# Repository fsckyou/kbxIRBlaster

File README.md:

# What the fork?
Yep, this project is a fork of the fantastic open hardware designed by Keith Burzinkski. Check out [the awesome design that this fork is based on](https://github.com/kbx81/kbxIRBlaster)! In many ways, this project is inferior to what he made, but intentionally inferior!

# Why the fork?
I used to buy Tuya IR blasters, pop them open and re-flash the firmware with ESPhome Like many IoT folks used to do. Then they stopped including wifi modules compatible with ESPhome. Well, left with no alternative, I guess I'll have to make them myself! A quick search found Keith's project which met most of my goals, but he designed it for high quality, maximum flexibility, and convenience of the user. My goal is primarily low cost, similarity to the old Tuya products, and bonus points if it can be assembled by JLC PCB.

# kbx and fsckyou IR Blaster

## What?

Just another ESP8266-based IR Blaster. It was designed with
 [ESPHome](https://esphome.io) in mind but should work fine with
 [Tasmota](https://tasmota.github.io/docs/) or any other app, really.

This design is round and should be pretty omnidirectional similar to the Tuya products you can buy on Amazon or Aliexpress.

I'll post images once I have them produced. As of now, this is only a design in progress.

## How?

I'll fill this part in later once the design is more final. ;)

 ## Legal stuff and License

The circuit schematics and PCB found here are licensed under the
 [Creative Commons Attribution-ShareAlike 4.0 International License](http://creativecommons.org/licenses/by-sa/4.0/).

_Happy building!_

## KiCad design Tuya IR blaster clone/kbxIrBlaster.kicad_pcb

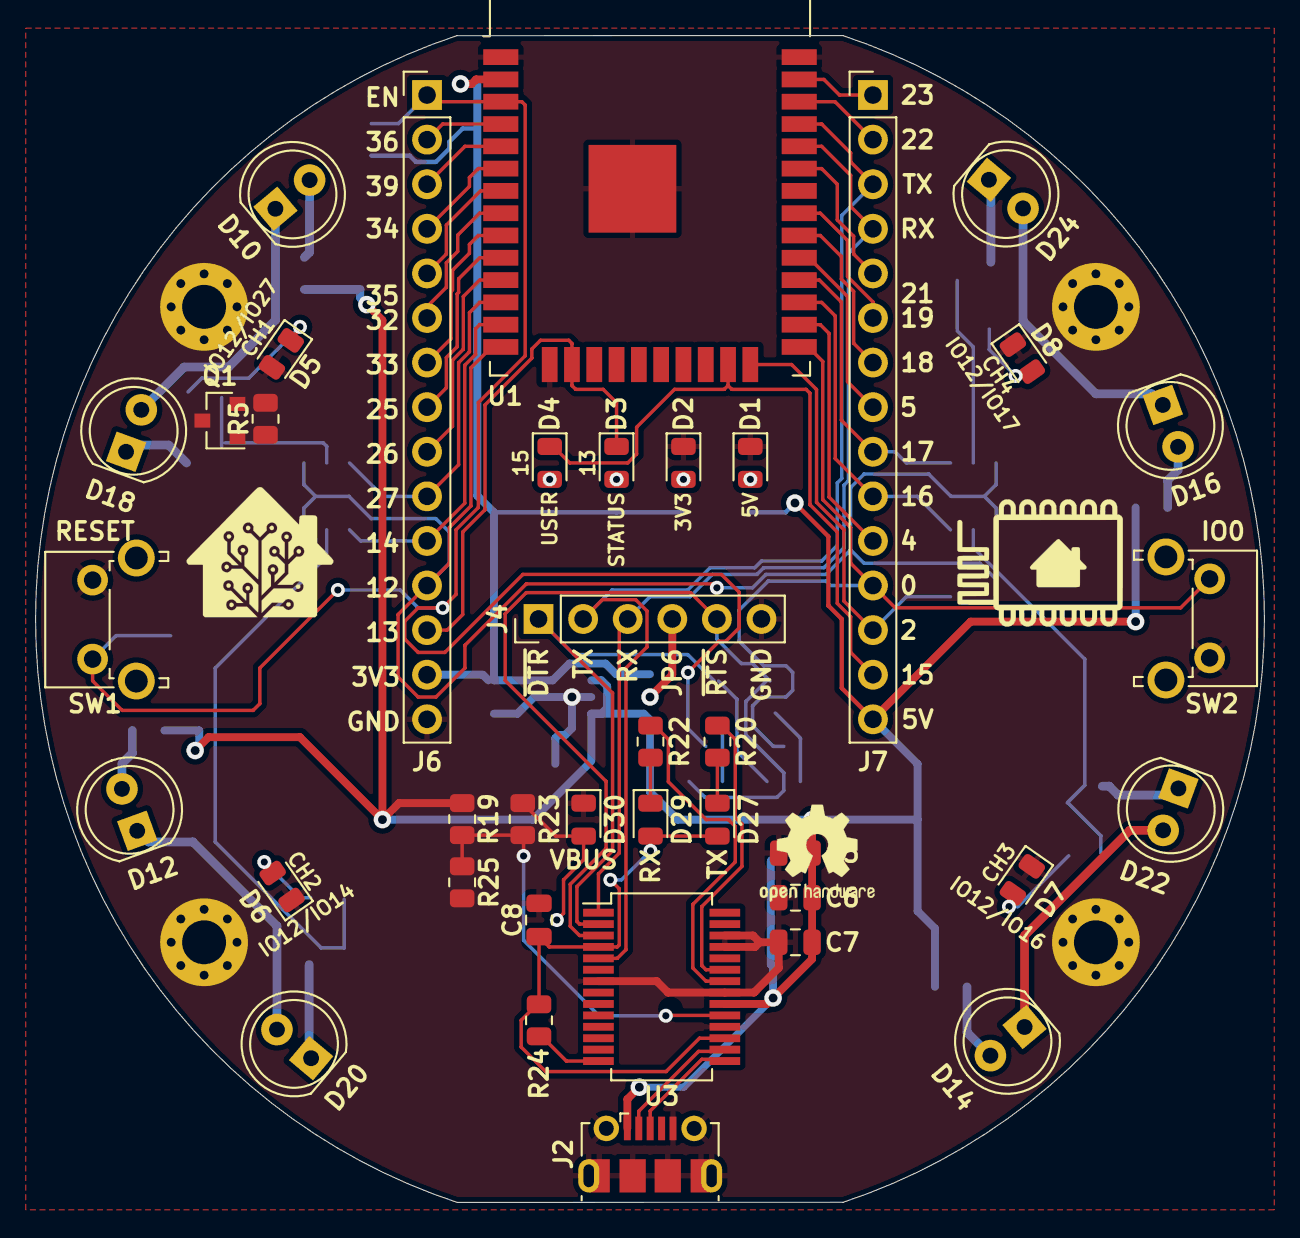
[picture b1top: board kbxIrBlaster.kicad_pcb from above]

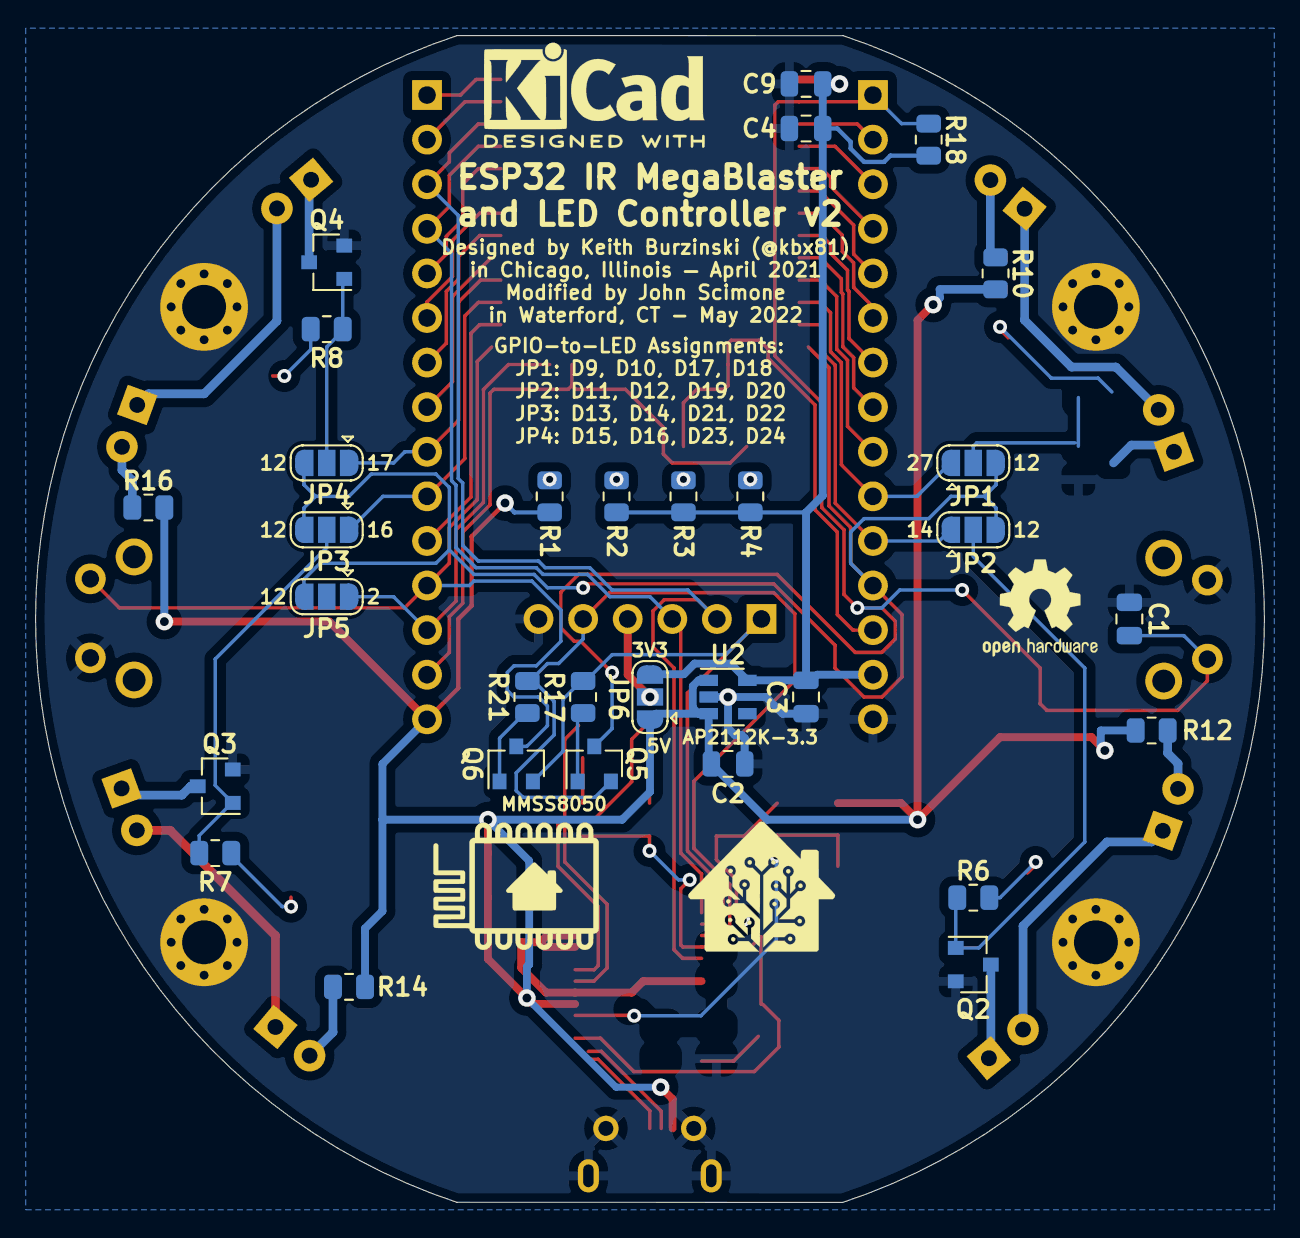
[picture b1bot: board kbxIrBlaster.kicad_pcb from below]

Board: 2 copper layers, 70.0 x 66.5 mm, 74 parts (31 on the bottom side), 69 nets.

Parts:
C1: 1 uF; C_0805_2012Metric
C2, C3, C4, C9: 10 uF; C_0805_2012Metric
C5: 4.7 uF; C_0805_2012Metric
C6, C7, C8: 100 nF; C_0805_2012Metric
D1: 5V; LED_0805_2012Metric
D2: 3V3; LED_0805_2012Metric
D3: STATUS; LED_0805_2012Metric
D4: USER; LED_0805_2012Metric
D5: CH1; LED_0805_2012Metric
D6: CH2; LED_0805_2012Metric
D7: CH3; LED_0805_2012Metric
D8: CH4; LED_0805_2012Metric
D10, D18: CH1; LED_D5.0mm
D12, D20: CH2; LED_D5.0mm
D14, D22: CH3; LED_D5.0mm
D16, D24: CH4; LED_D5.0mm
D27: TX; LED_0805_2012Metric
D29: RX; LED_0805_2012Metric
D30: VBUS; LED_0805_2012Metric
H1, H2, H3, H4: -; MountingHole_2.5mm_Pad_Via
J2: N/A; USB_Micro-B_Molex-105017-0001
J4: SERIAL; PinHeader_1x06_P2.54mm_Vertical
J6, J7: IO; PinHeader_1x15_P2.54mm_Vertical
JP1: IO12/IO27; SolderJumper-3_P1.3mm_Open_RoundedPad1.0x1.5mm
JP2: IO12/IO14; SolderJumper-3_P1.3mm_Open_RoundedPad1.0x1.5mm
JP3: IO12/IO16; SolderJumper-3_P1.3mm_Open_RoundedPad1.0x1.5mm
JP4: IO12/IO17; SolderJumper-3_P1.3mm_Open_RoundedPad1.0x1.5mm
JP5: IO12/IO2; SolderJumper-3_P1.3mm_Open_RoundedPad1.0x1.5mm
JP6: 5V/3V3; SolderJumper-3_P1.3mm_Open_RoundedPad1.0x1.5mm
Q1, Q2, Q3, Q4: 2N7002; SOT-23
Q5, Q6: MMSS8050; SOT-23
R1: 8K2; R_0805_2012Metric
R2: 1K6; R_0805_2012Metric
R3: 120; R_0805_2012Metric
R4, R20: 1K2; R_0805_2012Metric
R5, R6, R7, R8, R22: 2K7; R_0805_2012Metric
R10, R12, R14, R16: 27; R_0805_2012Metric
R17, R18, R21, R23, R24, R25: 10K; R_0805_2012Metric
R19: 4K7; R_0805_2012Metric
SW1: RESET; SW_Tactile_SPST_Angled_PTS645Vx58-2LFS
SW2: IO0; SW_Tactile_SPST_Angled_PTS645Vx58-2LFS
U1: ESP32-WROOM-32D; ESP32-WROOM-32
U2: AP2112K-3.3; SOT-23-5
U3: FT232RL; SSOP-28_5.3x10.2mm_P0.65mm

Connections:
+3V3: C3.2, C4.2, C9.2, J6.14, JP6.3 (B), R2.1, R3.1, R4.1, R18.1, U1.2 (VDD), U2.5 (VOUT)
+5V: C2.2, C5.1, C6.1, C7.1, J2.1 (VBUS), J7.15, JP6.1 (A), R1.1, R10.1, R12.1, R14.1, R16.1, R19.2, U2.1 (VIN), U2.3 (EN), U3.20 (VCC)
/ESP_EN: C1.1, J6.1, Q5.3 (C), R18.2, SW1.1, U1.3 (EN)
/ESP_RXD: J4.3, J7.4, U1.34 (RXD0/IO3), U3.1 (TXD)
/ESP_TXD: J4.2, J7.3, U1.35 (TXD0/IO1), U3.5 (RXD)
/FET1: D18.1 (K), Q1.3 (D)
/FET2: D20.1 (K), Q2.3 (D)
/FET3: D22.1 (K), Q3.3 (D)
/FET4: D24.1 (K), Q4.3 (D)
/GATE1: JP1.2 (C), Q1.1 (G), R5.1
/GATE2: JP2.2 (C), Q2.1 (G), R6.1
/GATE3: JP3.2 (C), Q3.1 (G), R7.1
/GATE4: JP4.2 (C), Q4.1 (G), R8.1
/GPI34: J6.4, U1.6 (IO34)
/GPI35: J6.5, U1.7 (IO35)
/GPI36: J6.2, U1.4 (SENSOR_VP)
/GPI39: J6.3, U1.5 (SENSOR_VN)
/GPIO0: J7.12, Q6.3 (C), SW2.1, U1.25 (IO0)
/GPIO2: J7.13, JP5.1 (A), U1.24 (IO2)
/GPIO4: J7.11, U1.26 (IO4)
/GPIO5: J7.8, U1.29 (IO5)
/GPIO12: J6.12, JP1.3 (B), JP2.3 (B), JP3.3 (B), JP4.3 (B), JP5.3 (B), U1.14 (IO12)
/GPIO13: D3.1 (K), J6.13, U1.16 (IO13)
/GPIO14: J6.11, JP2.1 (A), U1.13 (IO14)
/GPIO15: D4.1 (K), J7.14, U1.23 (IO15)
/GPIO16: J7.10, JP3.1 (A), U1.27 (IO16)
/GPIO17: J7.9, JP4.1 (A), U1.28 (IO17)
/GPIO18: J7.7, U1.30 (IO18)
/GPIO19: J7.6, U1.31 (IO19)
/GPIO21: J7.5, U1.33 (IO21)
/GPIO22: J7.2, U1.36 (IO22)
/GPIO23: J7.1, U1.37 (IO23)
/GPIO25: J6.8, U1.10 (IO25)
/GPIO26: J6.9, U1.11 (IO26)
/GPIO27: J6.10, JP1.1 (A), U1.12 (IO27)
/GPIO32: J6.6, U1.8 (IO32)
/GPIO33: J6.7, U1.9 (IO33)
/USB_D+: J2.3 (D+), U3.15 (USBD+)
/USB_D-: J2.2 (D-), U3.16 (USBD-)
/USB_~RESET: R19.1, R23.2, R25.2, U3.19 (~RESET)
/~DTR: J4.1, Q6.2 (E), R17.2, U3.2 (DTR)
/~RTS: J4.5, Q5.2 (E), R21.2, U3.3 (RTS)
GND: C1.2, C2.1, C3.1, C4.1, C5.2, C6.2, C7.2, C8.2, C9.1, D1.1 (K), D2.1 (K), D5.1 (K), D6.1 (K), D7.1 (K), D8.1 (K), D30.1 (K), H1.1, H2.1, H3.1, H4.1, J2.5 (GND), J2.6 (Shield), J4.6, J6.15, Q1.2 (S), Q2.2 (S), Q3.2 (S), Q4.2 (S), R25.1, SW1.2, SW2.2, U1.1 (GND), U1.15 (GND), U1.38 (GND), U1.39 (GND), U2.2 (GND), U3.7 (GND), U3.18 (GND), U3.21 (GND), U3.25 (AGND), U3.26 (TEST)
unnamed: C8.1, D27.2 (A), D29.2 (A), R24.1, U3.4 (VCCIO), U3.17 (3V3OUT)
unnamed: D1.2 (A), R1.2
unnamed: D2.2 (A), R2.2
unnamed: D3.2 (A), R3.2
unnamed: D4.2 (A), R4.2
unnamed: D5.2 (A), R5.2
unnamed: D10.1 (K), D18.2 (A)
unnamed: D10.2 (A), R10.2
unnamed: D12.1 (K), D20.2 (A)
unnamed: D12.2 (A), R12.2
unnamed: D14.1 (K), D22.2 (A)
unnamed: D14.2 (A), R14.2
unnamed: D16.1 (K), D24.2 (A)
unnamed: D16.2 (A), R16.2
unnamed: D27.1 (K), R20.1
unnamed: D29.1 (K), R22.1
unnamed: D30.2 (A), R23.1
unnamed: J4.4, JP6.2 (C)
unnamed: Q5.1 (B), R17.1
unnamed: Q6.1 (B), R21.1
unnamed: D6.2 (A), R6.2
unnamed: D7.2 (A), R7.2
unnamed: D8.2 (A), R8.2
unnamed: R20.2, U3.23 (CBUS0)
unnamed: R22.2, U3.22 (CBUS1)
unnamed: R24.2, U3.14 (CBUS3)

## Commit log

2022-05-02 Removed v1 folder and renamed v2 folder. Started making schematic and layout changes.

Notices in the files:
README.md:
Creative Commons License badge
